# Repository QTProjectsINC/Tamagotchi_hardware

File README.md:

# Tamagotchi_hardware
PCB for tamagotchi project

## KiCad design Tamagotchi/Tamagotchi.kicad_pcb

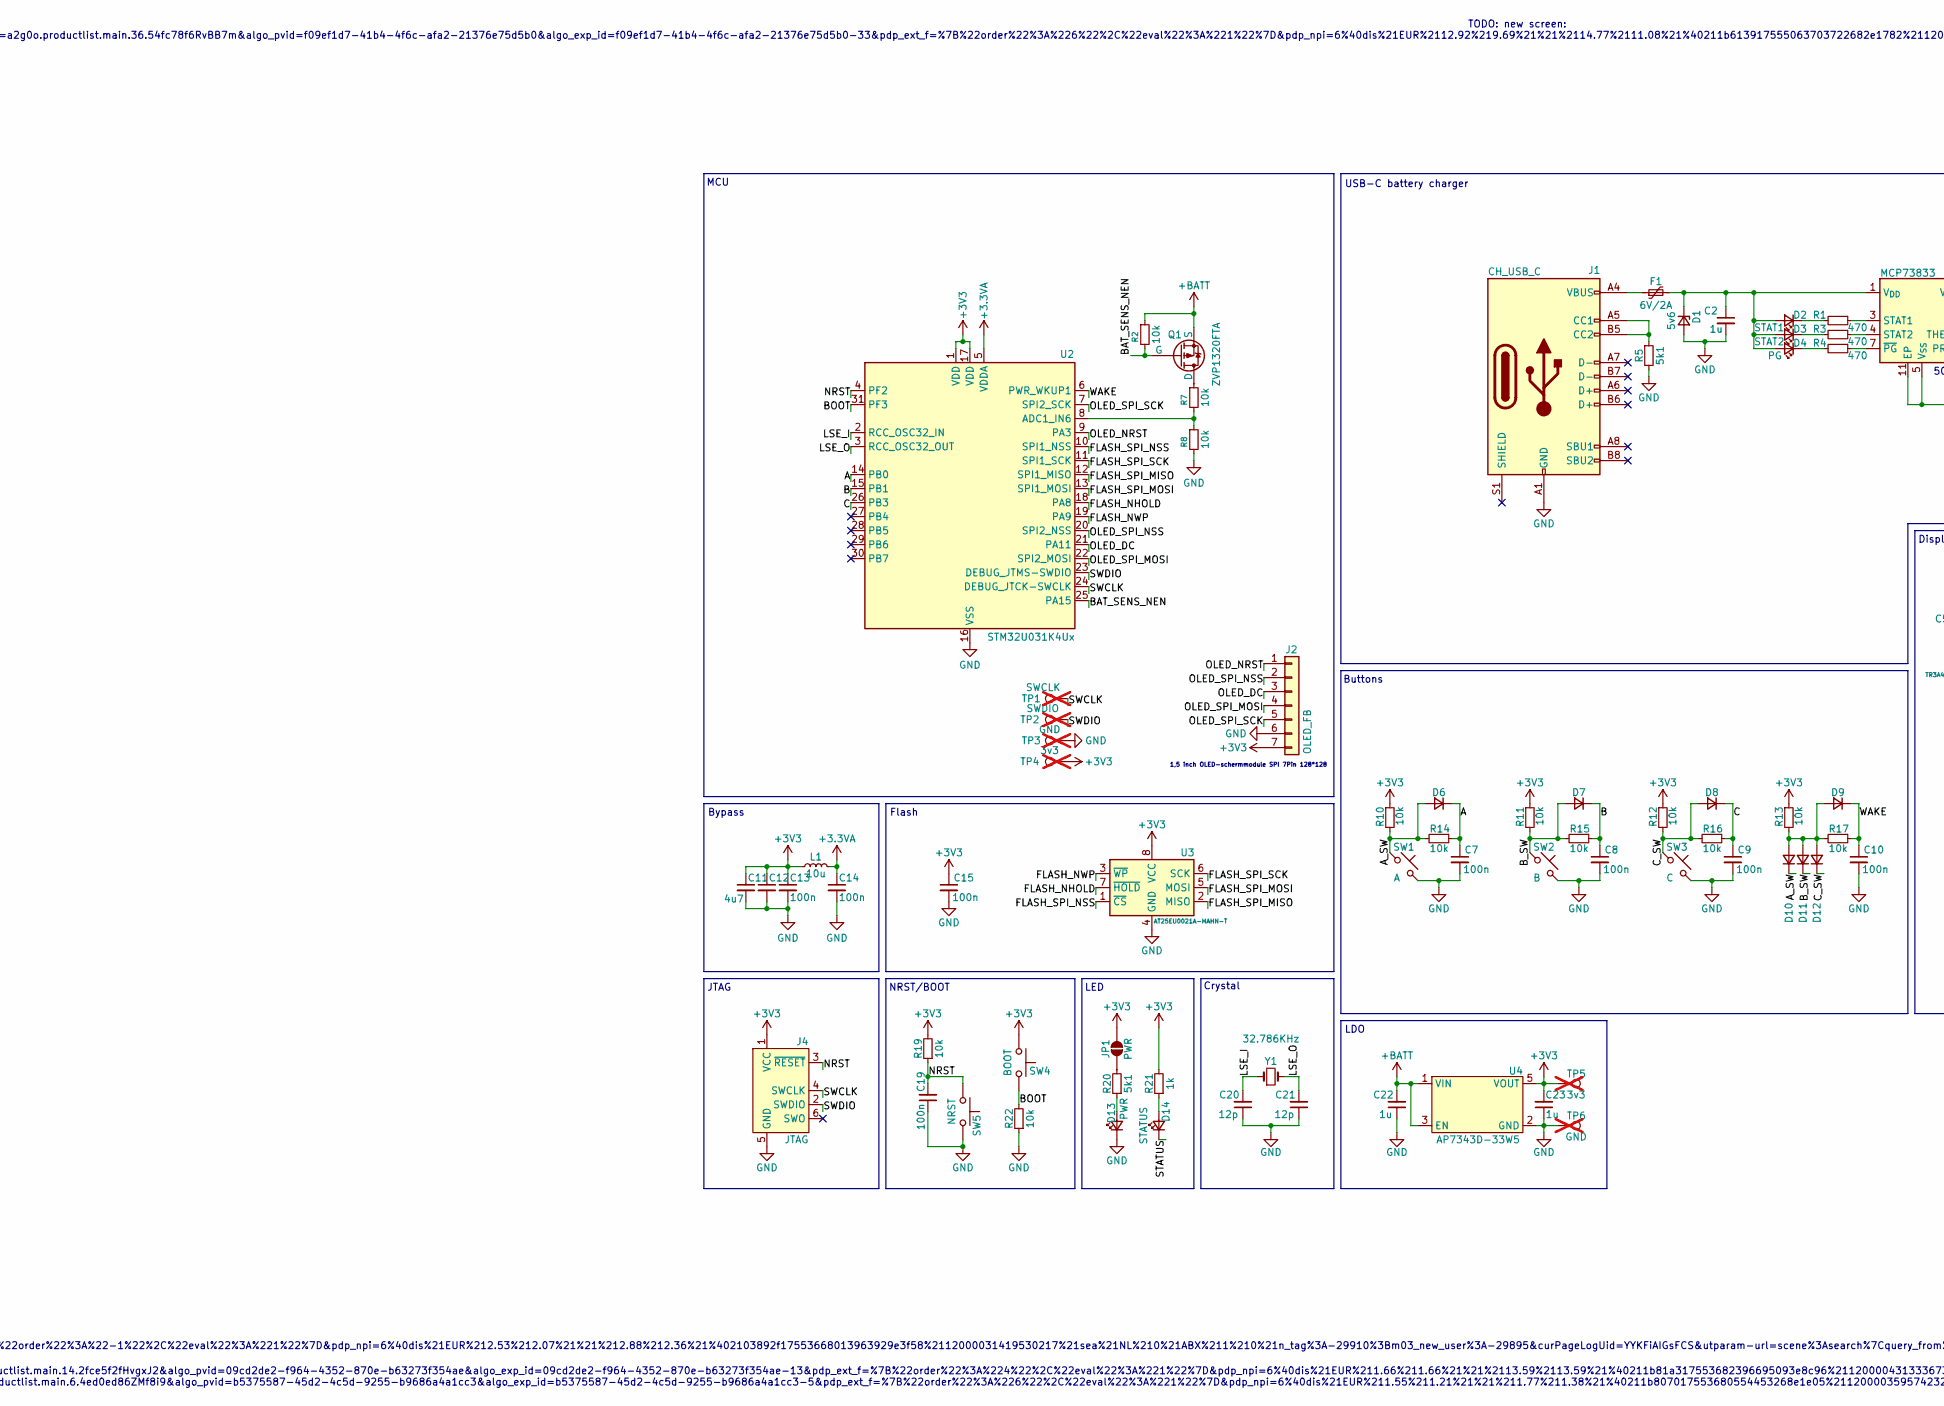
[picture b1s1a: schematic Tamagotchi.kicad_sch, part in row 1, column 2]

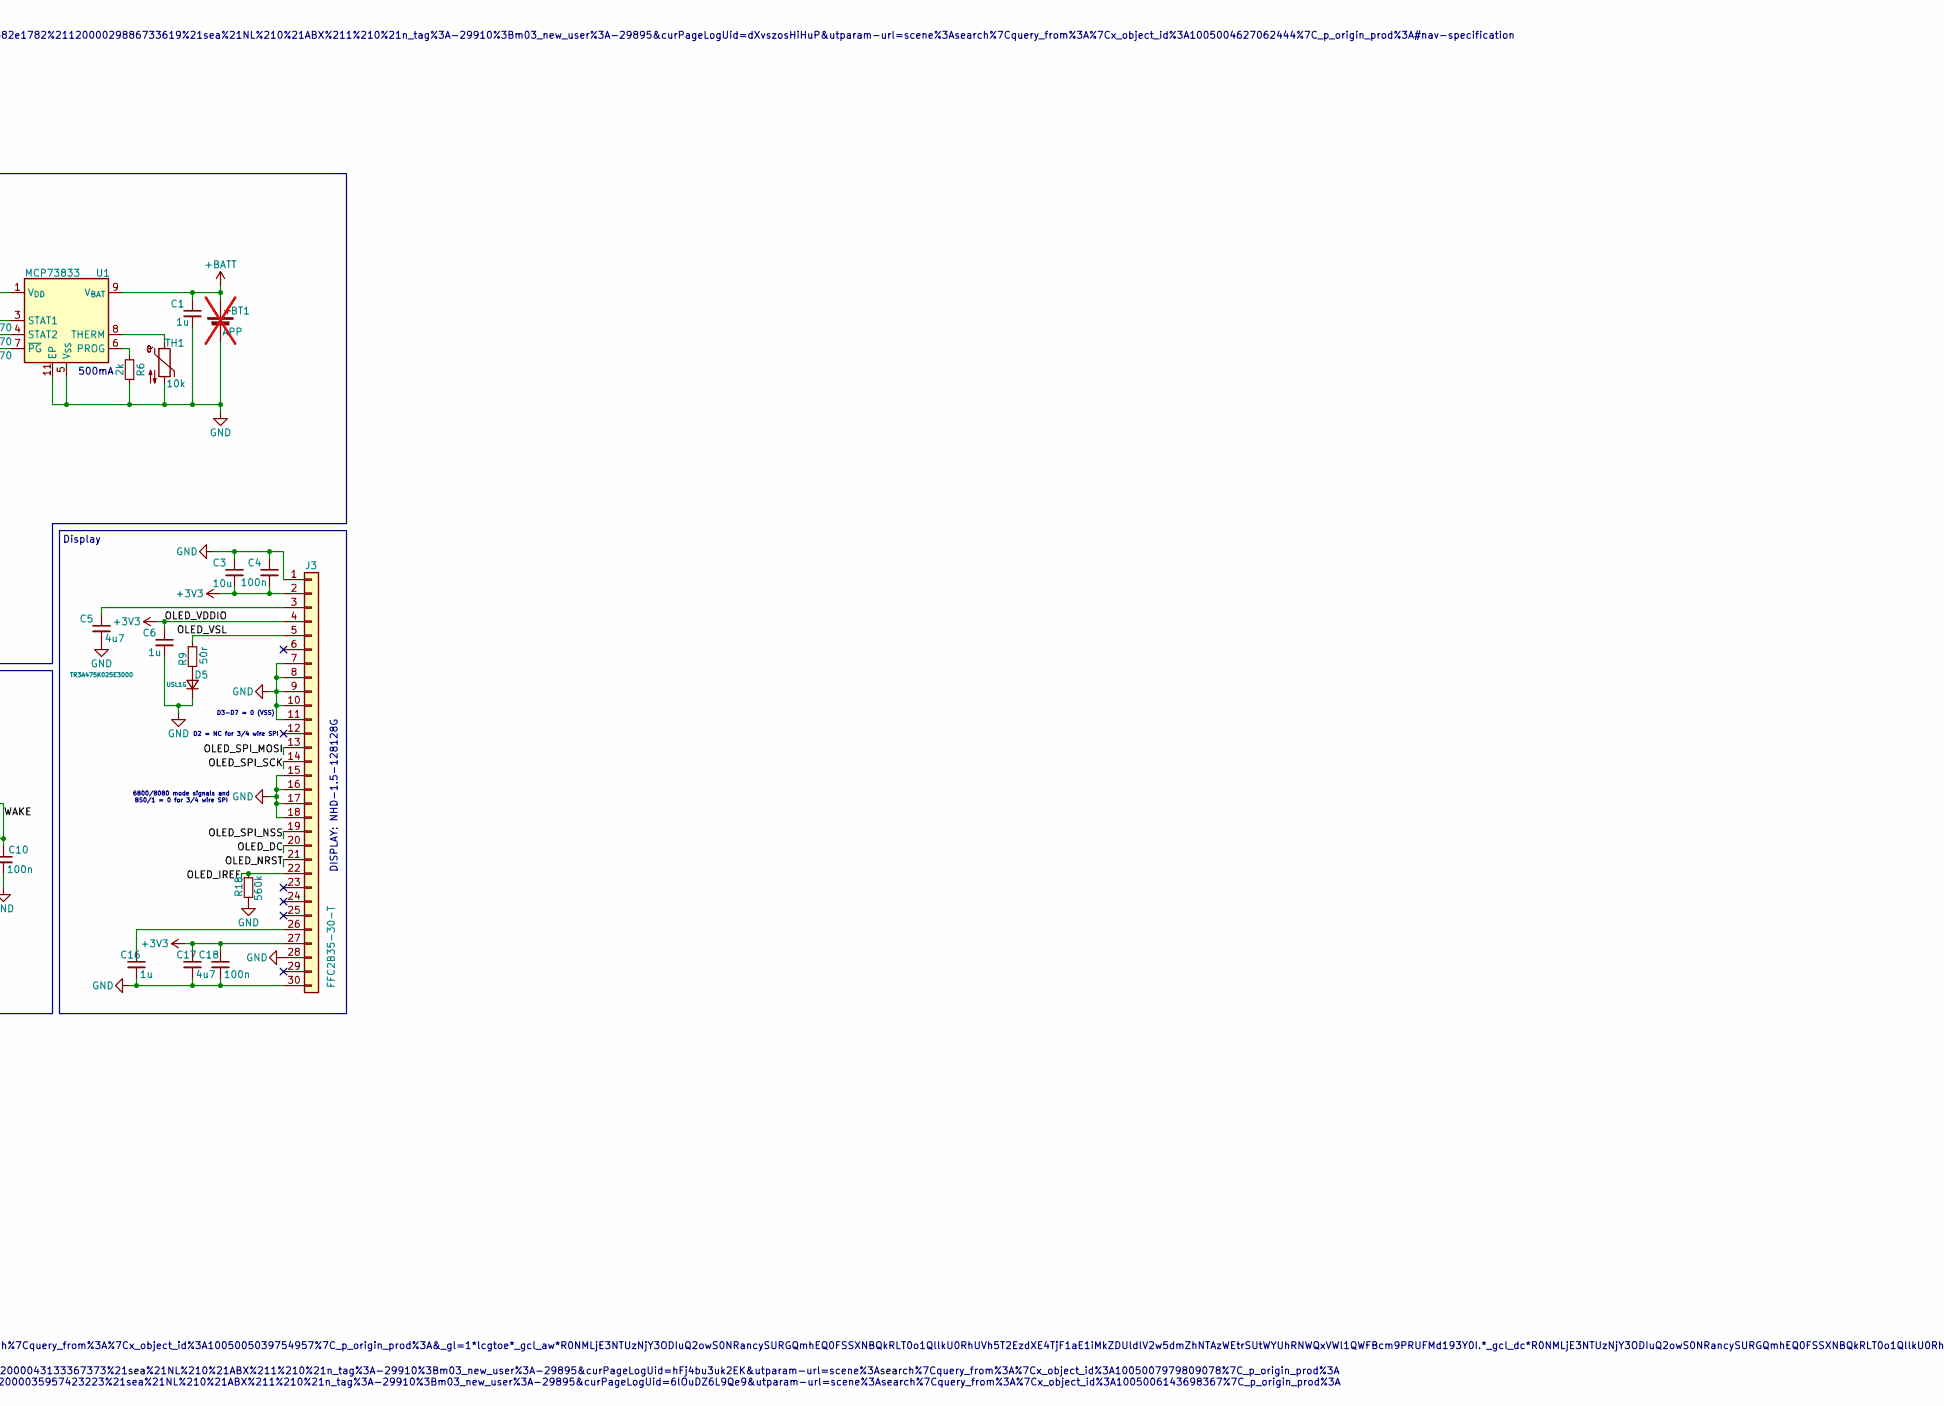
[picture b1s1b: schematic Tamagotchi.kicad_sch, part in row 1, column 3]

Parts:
BT1: APP; PinHeader_1x02_P2.54mm_Vertical; not fitted
C1, C2: 1u; C_0603_1608Metric; mouser 963-MLAST168SB7105KT
C3: 10u; C_0603_1608Metric
C4, C7, C8, C9, C10, C12, C13, C14, C15, C18, C19: 100n; C_0603_1608Metric
C5: 4u7; CP_EIA-3216-18_Kemet-A; mouser 74-TR3A475K025E3000
C6, C16, C22, C23: 1u; C_0603_1608Metric
C11, C17: 4u7; C_0603_1608Metric
C20, C21: 12p; C_0603_1608Metric
D1: 5v6; D_SOD-123; mouser 78-BZT52C5V6-E3-08
D2: STAT1; LED_0603_1608Metric; mouser 710-150060AS75000
D3: STAT2; LED_0603_1608Metric; mouser 710-150060AS75000
D4: PG; LED_0603_1608Metric; mouser 710-150060RS75000
D5: USL1G; D_SOD-123F
D6, D7, D8, D9, D10, D11, D12: SOD-523F; mouser 750-CDBU0245
D13: PWR; LED_0603_1608Metric; mouser 710-150060AS75000
D14: STATUS; LED_0603_1608Metric; mouser 710-150060AS75000
F1: 6V/2A; Fuse_1206_3216Metric; mouser 504-PTS18126V260
J1: CH_USB_C; USB_C_Receptacle_HCTL_HC-TYPE-C-16P-01A
J2: OLED_FB; PinHeader_1x07_P2.54mm_Vertical
J3: FFC2B35-30-T; FFC2B35-30
J4: JTAG; Tag-Connect_TC2030-IDC-FP_2x03_P1.27mm_Vertical
JP1: PWR; SolderJumper-2_P1.3mm_Open_TrianglePad1.0x1.5mm
L1: 10u; L_0805_2012Metric
Q1: ZVP1320FTA; SOT-323; mouser 522-ZVP1320FTA
R1, R3, R4: 470; R_0603_1608Metric; LCSC C23186
R2, R7, R8, R10, R11, R12, R13, R14, R15, R16, R17, R19, R22: 10k; R_0603_1608Metric
R5: 5k1; R_0603_1608Metric; LCSC C23186
R6: 2k; R_0603_1608Metric; LCSC C23186
R9: 50r; R_0603_1608Metric
R18: 560k; R_0603_1608Metric
R20: 5k1; R_0603_1608Metric
R21: 1k; R_0603_1608Metric
SW1: A; TSF-1178Z
SW2: B; TSF-1178Z
SW3: C; TSF-1178Z
SW4: BOOT; SW_SPST_PTS810; LCSC C2681476
SW5: NRST; SW_SPST_PTS810; LCSC C2681476
TH1: 10k; R_0603_1608Metric; mouser 667-ERT-J1VR103J
TP1: SWCLK; TestPoint_Pad_D1.5mm; not fitted
TP2: SWDIO; TestPoint_Pad_D1.5mm; not fitted
TP3, TP6: GND; TestPoint_Pad_D1.5mm; not fitted
TP4, TP5: 3v3; TestPoint_Pad_D1.5mm; not fitted
U1: MCP73833; DFN-10-1EP_3x3mm_P0.5mm_EP1.58x2.35mm; mouser 579-MCP73833T-AMI/MF
U2: STM32U031K4Ux; QFN-32-1EP_5x5mm_P0.5mm_EP3.45x3.45mm
U3: AT25EU0021A-MAHN-T; DFN-8-1EP_3x2mm_P0.5mm_EP1.75x1.45mm
U4: AP7343D-33W5; SOT-25
Y1: 32.786KHz; Crystal_SMD_3215-2Pin_3.2x1.5mm

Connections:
+3.3VA: C14.1, L1.2, U2.5 (VDDA)
+3V3: C3.2, C4.2, C6.1, C11.1, C12.1, C13.1, C15.1, C17.1, C18.1, C23.2, J2.7, J3.2, J3.4, J3.27, J4.1 (VCC), JP1.2 (B), L1.1, R10.1, R11.1, R12.1, R13.1, R19.2, R21.2, SW4.1, TP4.1, TP5.1, U2.1 (VDD), U2.17 (VDD), U3.8 (VCC), U4.5 (VOUT)
+BATT: BT1.1 (+), C1.1, C22.2, Q1.3 (S), R2.1, U1.9 (V_{BAT}), U1.10 (V_{BAT}), U4.1 (VIN), U4.3 (EN)
/A: C7.1, D6.1 (K), R14.1, U2.14 (PB0)
/A_SW: D6.2 (A), D10.1 (K), R10.2, R14.2, SW1.1
/B: C8.1, D7.1 (K), R15.1, U2.15 (PB1)
/BAT_SENS_NEN: Q1.2 (G), R2.2, U2.25 (PA15)
/BOOT: R22.2, SW4.2, U2.31 (PF3)
/B_SW: D7.2 (A), D11.1 (K), R11.2, R15.2, SW2.1
/C: C9.1, D8.1 (K), R16.1, U2.26 (PB3)
/C_SW: D8.2 (A), D12.1 (K), R12.2, R16.2, SW3.1
/FLASH_NHOLD: U2.18 (PA8), U3.7 (~HOLD)
/FLASH_NWP: U2.19 (PA9), U3.3 (~WP)
/FLASH_SPI_MISO: U2.12 (SPI1_MISO), U3.2 (MISO)
/FLASH_SPI_MOSI: U2.13 (SPI1_MOSI), U3.5 (MOSI)
/FLASH_SPI_NSS: U2.10 (SPI1_NSS), U3.1 (~CS)
/FLASH_SPI_SCK: U2.11 (SPI1_SCK), U3.6 (SCK)
/LSE_I: C20.2, U2.2 (RCC_OSC32_IN), Y1.1
/LSE_O: C21.2, U2.3 (RCC_OSC32_OUT), Y1.2
/NRST: C19.2, J4.3 (~RESET), R19.1, SW5.1, U2.4 (PF2)
/OLED_DC: J2.3, J3.20, U2.21 (PA11)
/OLED_IREF: J3.22, R18.1
/OLED_NRST: J2.1, J3.21, U2.9 (PA3)
/OLED_SPI_MOSI: J2.4, J3.13, U2.22 (SPI2_MOSI)
/OLED_SPI_NSS: J2.2, J3.19, U2.20 (SPI2_NSS)
/OLED_SPI_SCK: J2.5, J3.14, U2.7 (SPI2_SCK)
/OLED_VSL: J3.5, R9.1
/STATUS: D14.1 (K)
/SWCLK: J4.4 (SWCLK), TP1.1, U2.24 (DEBUG_JTCK-SWCLK)
/SWDIO: J4.2 (SWDIO), TP2.1, U2.23 (DEBUG_JTMS-SWDIO)
/WAKE: C10.1, D9.1 (K), R17.1, U2.6 (PWR_WKUP1)
GND: BT1.2 (-), C1.2, C2.2, C3.1, C4.1, C5.2, C6.2, C7.2, C8.2, C9.2, C10.2, C11.2, C12.2, C13.2, C14.2, C15.2, C16.2, C17.2, C18.2, C19.1, C20.1, C21.1, C22.1, C23.1, D1.2 (A), D5.1 (K), D13.1 (K), J1.A1 (GND), J1.A12 (GND), J1.B1 (GND), J1.B12 (GND), J2.6, J3.1, J3.7, J3.8, J3.9, J3.10, J3.11, J3.15, J3.16, J3.17, J3.18, J3.28, J3.30, J4.5 (GND), R5.2, R6.1, R8.2, R18.2, R22.1, SW1.2, SW2.2, SW3.2, SW5.2, TH1.2, TP3.1, TP6.1, U1.5 (V_{SS}), U1.11 (EP), U2.16 (VSS), U2.32 (VSS), U2.33 (VSS), U3.4 (GND), U3.9 (GND), U4.2 (GND)
unnamed: C2.1, D1.1 (K), D2.2 (A), D3.2 (A), D4.2 (A), F1.2, U1.1 (V_{DD}), U1.2 (V_{DD})
unnamed: D2.1 (K), R1.2
unnamed: D3.1 (K), R3.2
unnamed: D4.1 (K), R4.2
unnamed: D5.2 (A), R9.2
unnamed: D9.2 (A), D10.2 (A), D11.2 (A), D12.2 (A), R13.2, R17.2
unnamed: D13.2 (A), R20.1
unnamed: D14.2 (A), R21.1
unnamed: F1.1, J1.A4 (VBUS), J1.A9 (VBUS), J1.B4 (VBUS), J1.B9 (VBUS)
unnamed: J1.A5 (CC1), J1.B5 (CC2), R5.1
unnamed: C5.1, J3.3
unnamed: C16.1, J3.26
unnamed: JP1.1 (A), R20.2
unnamed: Q1.1 (D), R7.1
unnamed: R6.2, U1.6 (PROG)
unnamed: R1.1, U1.3 (STAT1)
unnamed: R3.1, U1.4 (STAT2)
unnamed: TH1.1, U1.8 (THERM)
unnamed: R4.1, U1.7 (~PG)
unnamed: R7.2, R8.1, U2.8 (ADC1_IN6)

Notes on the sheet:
LDO
D3-D7 = 0 (VSS)
MCU
DISPLAY: https://nl.aliexpress.com/item/1005005039754957.html?spm=a2g0o.productlist.main.28.6ceaFg0hFg0hn5&algo_pvid=c510dd45-5260-4aa8-843d-e0720577f99c&algo_exp_id=c510dd45-5260-4aa8-843d-e0720577f99c-31&pdp_ext_f=%7B%22order%22%3A%22-1%22%2C%22eval%22%3A%221%22%7D&pdp_npi=6%40dis%21EUR%212.53%21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
Buttons
LED
Bypass
Display
Crystal
JTAG
USB-C battery charger
NRST/BOOT
1,5 inch OLED-schermmodule SPI 7Pin 128*128
TODO: new screen: https://nl.aliexpress.com/item/1005004627062444.html?spm=a2g0o.productlist.main.36.54fc78f6RvBB7m&algo_pvid=f09ef1d7-41b4-4f6c-afa2-21376e75d5b0&algo_exp_id=f09ef1d7-41b4-4f6c-afa2-21376e75d5b0-33&pdp_ext_f=%7B%22order%22%3A%226%22%2C%22eval%22%3A%221%22%7D&pdp_npi=6%40dis%21EUR%2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
Flash
BUTTON TH: https://nl.aliexpress.com/item/1005007979809078.html?spm=a2g0o.productlist.main.14.2fce5f2fHvgxJ2&algo_pvid=09cd2de2-f964-4352-870e-b63273f354ae&algo_exp_id=09cd2de2-f964-4352-870e-b63273f354ae-13&pdp_ext_f=%7B%22order%22%3A%224%22%2C%22eval%22%3A%221%22%7D&pdp_npi=6%40dis%21EUR%211.66%2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
D2 = NC for 3/4 wire SPI
DISPLAY: NHD-1.5-128128G
6800/8080 mode signals and BS0/1 = 0 for 3/4 wire SPI
500mA

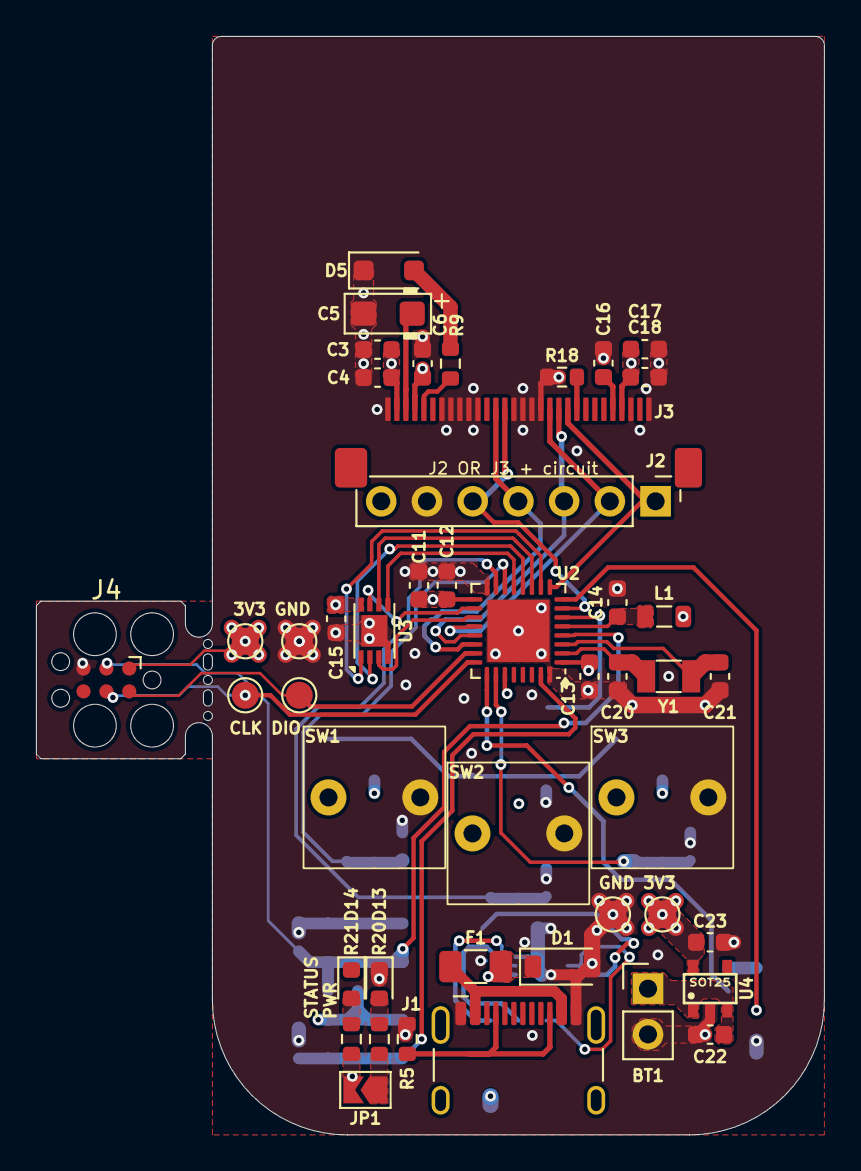
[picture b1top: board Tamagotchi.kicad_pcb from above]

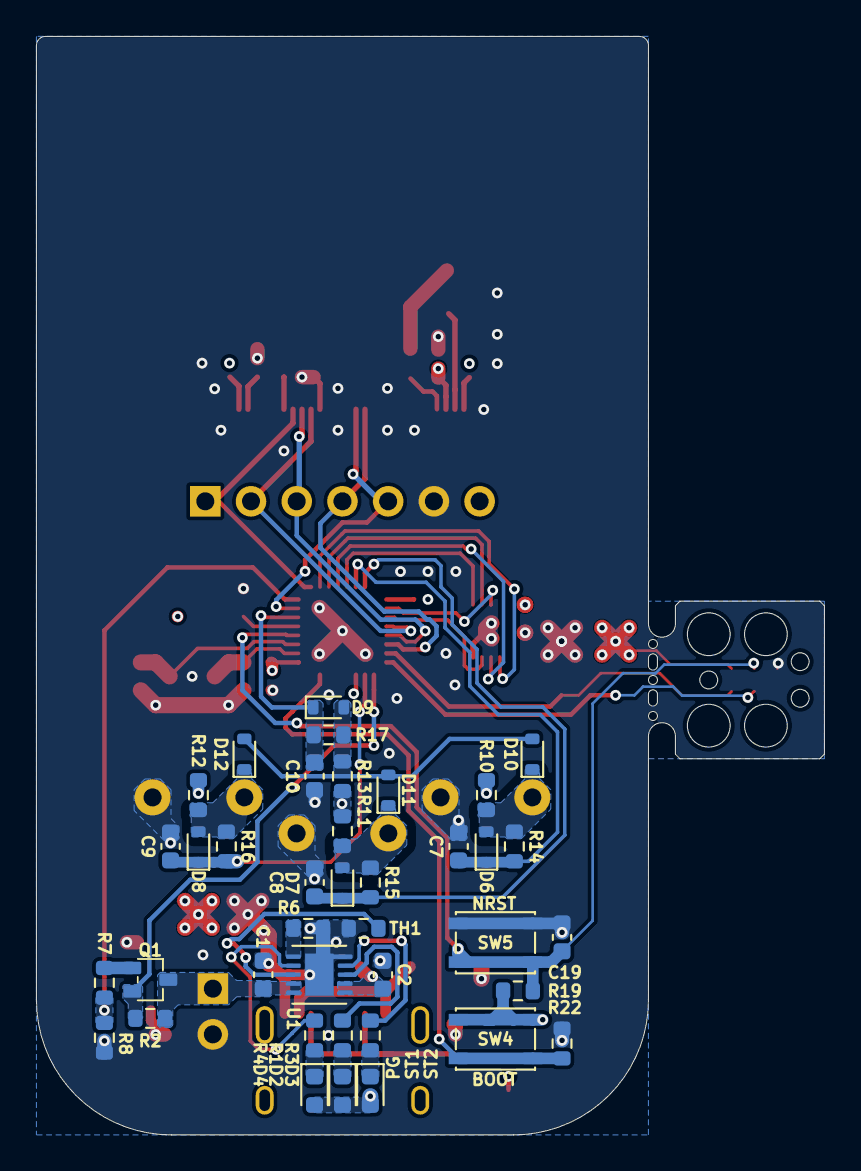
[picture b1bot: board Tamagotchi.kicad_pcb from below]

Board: 4 copper layers, 43.8 x 61.0 mm, 85 parts (39 on the bottom side), 51 nets.

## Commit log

2025-08-18 .85" LCD
2025-08-20 Fixed power section
2025-08-20 Removed old note
